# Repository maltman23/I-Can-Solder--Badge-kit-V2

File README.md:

# "I Can Solder" Badge kit V2

Anyone can learn to solder! This kit was designed for people who have never made anything before. Simple step-by-step instructions show you how. Once you finish, you get a cool colored blinky light badge you can wear. Plus, it doubles as a flashlight!

This kit takes about 30 minutes to complete.

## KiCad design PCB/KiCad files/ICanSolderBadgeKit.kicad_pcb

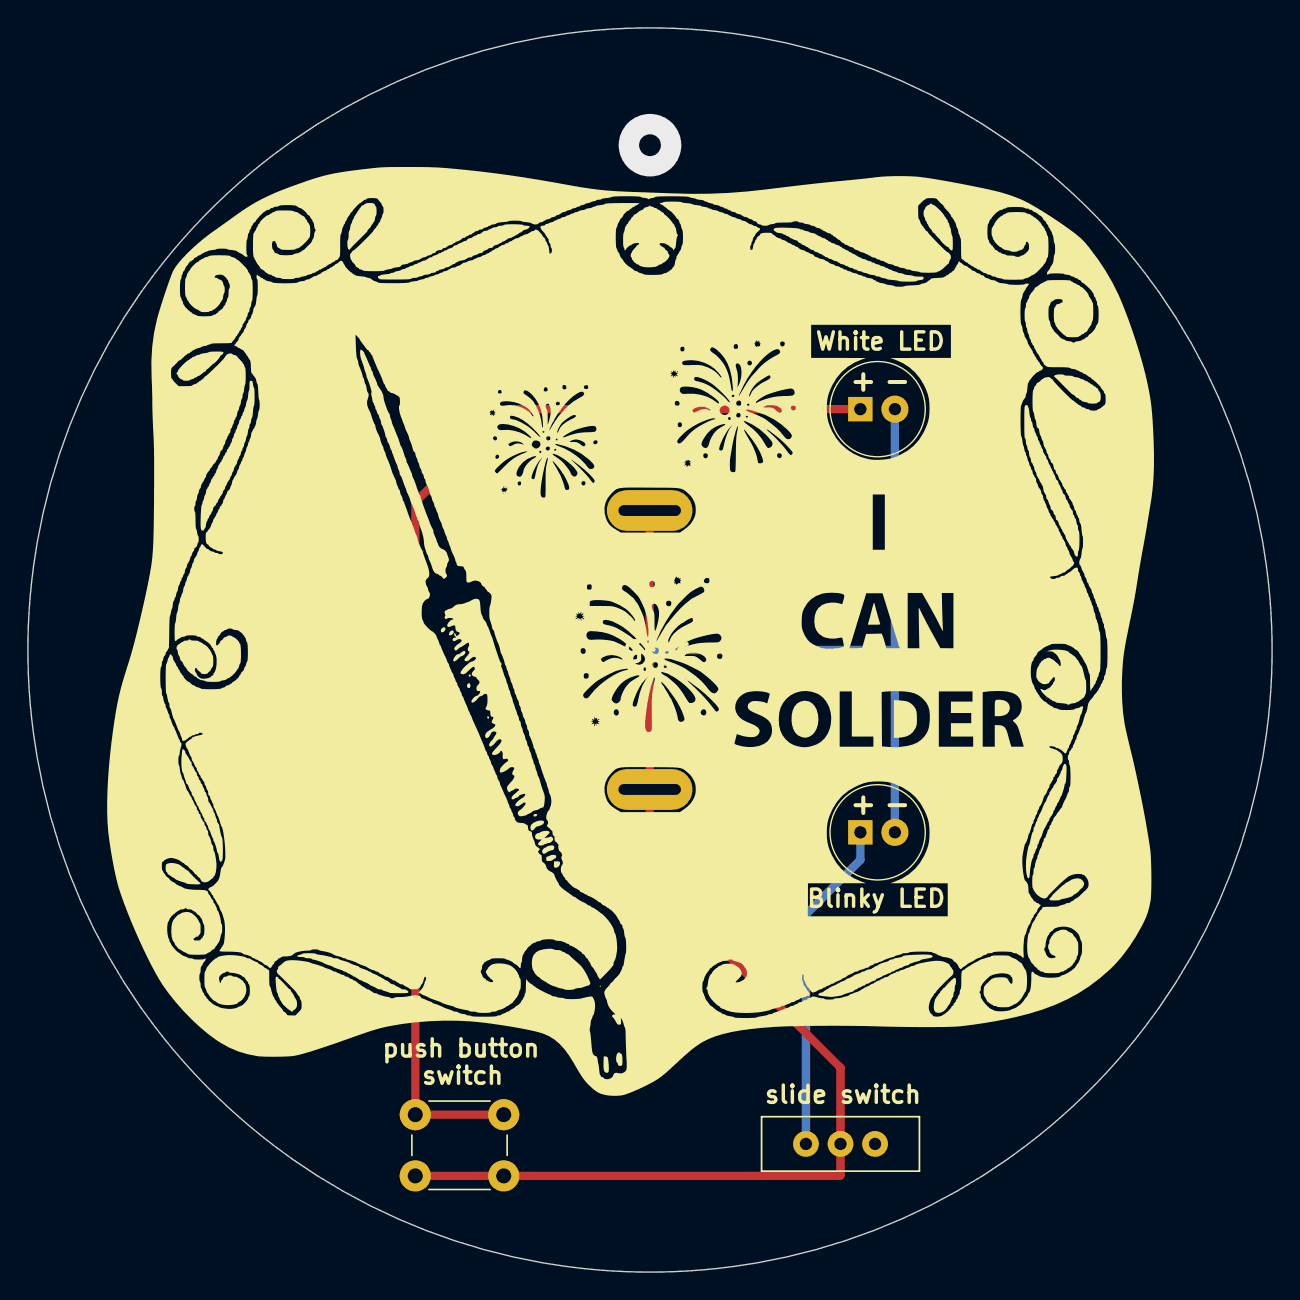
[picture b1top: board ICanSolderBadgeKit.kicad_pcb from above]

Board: 2 copper layers, 91.4 x 91.4 mm, 5 parts (1 on the bottom side), 4 nets.

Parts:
B1: CR2032; Keystone 3003 CR2032 batt holder
LED1: White LED; LED_D5.0mm
LED2: Blinky LED; LED_D5.0mm
SW1: push; SW_PUSH_tact_6mm_H4.3mm
SW2: slide; SW_MINI-SPDT-SW

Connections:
GND: B1.3 (GND), LED1.1 (K), LED2.1 (K)
unnamed: B1.1 (+3V), B1.2 (+3V), SW1.1, SW2.2
unnamed: LED1.2 (A), SW1.2
unnamed: LED2.2 (A), SW2.3

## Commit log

2023-06-28 "I Can Solder" Badge kit V2a
    Initial commit
2023-06-28 Create README.md
    Add README file
2023-06-28 Update README.md
    Fix copy-paste error in README file
2023-06-28 remove raw photos from repository
    remove raw photos from repository
